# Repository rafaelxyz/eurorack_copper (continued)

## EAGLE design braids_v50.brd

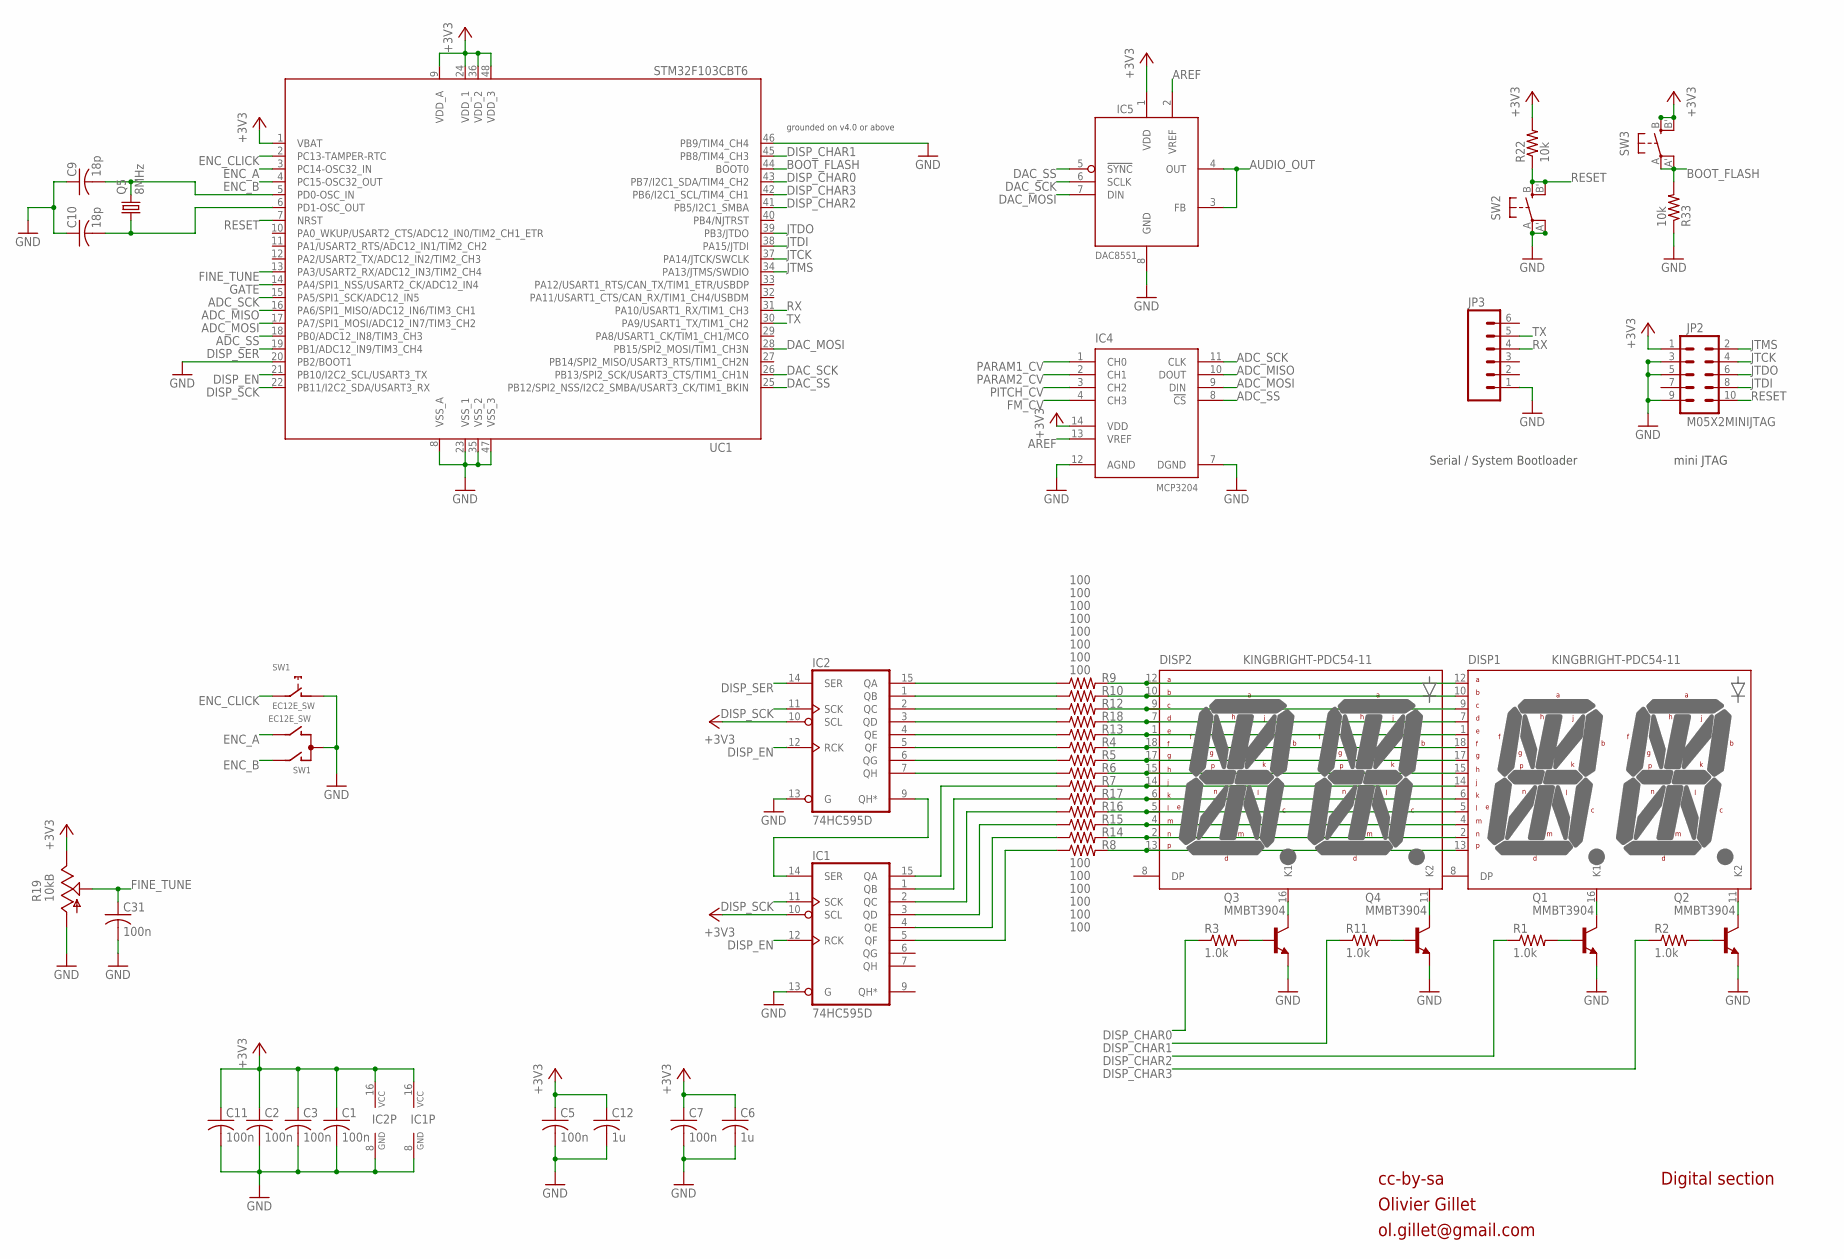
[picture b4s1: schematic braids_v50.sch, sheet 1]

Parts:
C1, C2, C3, C5, C7, C11, C31: 100n; C0603
C6, C12: 1u; C0603
C9, C10: 18p; C0603
DISP1, DISP2: KINGBRIGHT-PDC54-11; PDC54
IC1, IC2: 74HC595D; SO16
IC4: MCP3204; SO14
IC5: DAC8551; MSOP-8
JP2: M05X2MINIJTAG; 2X5-1.27
JP3: M06SIP; 1X06
Q1, Q2, Q3, Q4: MMBT3904; SOT23-BEC
Q5: 8MHz; HC49UP
R1, R2, R3, R11: 1.0k; R0603
R4, R5, R6, R7, R8, R9, R10, R12, R13, R14, R15, R16, R17, R18: 100; R0603
R19: 10kB; ALPS_POT_VERTICAL_PS
R22, R33: 10k; R0603
SW1: EC12E_SW; ALPS_EC12E_SW
SW2, SW3: EVQQ2; EVQ-Q2
UC1: STM32F103CBT6; LQFP48

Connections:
+3V3: C1.1, C2.1, C3.1, C5.1, C6.1, C7.1, C11.1, C12.1, IC1.10 (SCL), IC1.16 (VCC), IC2.10 (SCL), IC2.16 (VCC), IC4.14 (VDD), IC5.1 (VDD), JP2.1, R19.P$1 (E), R22.2, SW3.B (S), SW3.B' (S1), UC1.1 (VBAT), UC1.9 (VDD_A), UC1.24 (VDD_1), UC1.36 (VDD_2), UC1.48 (VDD_3); also elsewhere on the board
ADC_MISO: IC4.10 (DOUT), UC1.16 (PA6/SPI1_MISO/ADC12_IN6/TIM3_CH1)
ADC_MOSI: IC4.9 (DIN), UC1.17 (PA7/SPI1_MOSI/ADC12_IN7/TIM3_CH2)
ADC_SCK: IC4.11 (CLK), UC1.15 (PA5/SPI1_SCK/ADC12_IN5)
ADC_SS: IC4.8 (!CS), UC1.18 (PB0/ADC12_IN8/TIM3_CH3)
AREF: IC4.13 (VREF), IC5.2 (VREF); also elsewhere on the board
AUDIO_OUT: IC5.3 (FB), IC5.4 (OUT); also elsewhere on the board
BOOT_FLASH: R33.2, SW3.A, SW3.A' (P1), UC1.44 (BOOT0)
DAC_MOSI: IC5.7 (DIN), UC1.28 (PB15/SPI2_MOSI/TIM1_CH3N)
DAC_SCK: IC5.6 (SCLK), UC1.26 (PB13/SPI2_SCK/USART3_CTS/TIM1_CH1N)
DAC_SS: IC5.5 (!SYNC), UC1.25 (PB12/SPI2_NSS/I2C2_SMBA/USART3_CK/TIM1_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)
DISP_CHAR0: R3.1, UC1.43 (PB7/I2C1_SDA/TIM4_CH2)
DISP_CHAR1: R11.1, UC1.45 (PB8/TIM4_CH3)
DISP_CHAR2: R1.1, UC1.41 (PB5/I2C1_SMBA)
DISP_CHAR3: R2.1, UC1.42 (PB6/I2C1_SCL/TIM4_CH1)
DISP_EN: IC1.12 (RCK), IC2.12 (RCK), UC1.21 (PB10/I2C2_SCL/USART3_TX)
DISP_SCK: IC1.11 (SCK), IC2.11 (SCK), UC1.22 (PB11/I2C2_SDA/USART3_RX)
DISP_SER: IC2.14 (SER), UC1.19 (PB1/ADC12_IN9/TIM3_CH4)
ENC_A: SW1.B, UC1.3 (PC14-OSC32_IN)
ENC_B: SW1.A, UC1.4 (PC15-OSC32_OUT)
ENC_CLICK: SW1.E (2), UC1.2 (PC13-TAMPER-RTC)
FINE_TUNE: C31.1, R19.P$2 (S), UC1.13 (PA3/USART2_RX/ADC12_IN3/TIM2_CH4)
FM_CV: IC4.4 (CH3); also elsewhere on the board
GATE: UC1.14 (PA4/SPI1_NSS/USART2_CK/ADC12_IN4); also elsewhere on the board
GND: C1.2, C2.2, C3.2, C5.2, C6.2, C7.2, C9.1, C10.1, C11.2, C12.2, C31.2, IC1.8 (GND), IC1.13 (G), IC2.8 (GND), IC2.13 (G), IC4.7 (DGND), IC4.12 (AGND), IC5.8 (GND), JP2.3, JP2.5, JP2.9, JP3.1, Q1.E, Q2.E, Q3.E, Q4.E, R19.P$3 (A), R33.1, SW1.C, SW1.D (1), SW2.A, SW2.A' (P1), UC1.8 (VSS_A), UC1.20 (PB2/BOOT1), UC1.23 (VSS_1), UC1.35 (VSS_2), UC1.46 (PB9/TIM4_CH4), UC1.47 (VSS_3); also elsewhere on the board
JTCK: JP2.4, UC1.37 (PA14/JTCK/SWCLK)
JTDI: JP2.8, UC1.38 (PA15/JTDI)
JTDO: JP2.6, UC1.39 (PB3/JTDO)
JTMS: JP2.2, UC1.34 (PA13/JTMS/SWDIO)
unnamed: DISP2.16 (K1), Q3.C
unnamed: DISP2.11 (K2), Q4.C
unnamed: DISP1.16 (K1), Q1.C
unnamed: DISP1.11 (K2), Q2.C
unnamed: Q3.B, R3.2
unnamed: Q4.B, R11.2
unnamed: C9.2, Q5.2, UC1.5 (PD0-OSC_IN)
unnamed: C10.2, Q5.1, UC1.6 (PD1-OSC_OUT)
unnamed: Q1.B, R1.2
unnamed: Q2.B, R2.2
unnamed: DISP1.12 (A), DISP2.12 (A), R9.2
unnamed: DISP1.10 (B), DISP2.10 (B), R10.2
unnamed: DISP1.9 (C), DISP2.9 (C), R12.2
unnamed: DISP1.7 (D), DISP2.7 (D), R18.2
unnamed: DISP1.1 (E), DISP2.1 (E), R13.2
unnamed: DISP1.18 (F), DISP2.18 (F), R4.2
unnamed: DISP1.17 (G), DISP2.17 (G), R5.2
unnamed: DISP1.15 (H), DISP2.15 (H), R6.2
unnamed: DISP1.14 (J), DISP2.14 (J), R7.2
unnamed: DISP1.6 (K), DISP2.6 (K), R17.2
unnamed: DISP1.5 (L), DISP2.5 (L), R16.2
unnamed: DISP1.4 (M), DISP2.4 (M), R15.2
unnamed: DISP1.2 (N), DISP2.2 (N), R14.2
unnamed: DISP1.13, DISP2.13, R8.2
unnamed: IC2.7 (QH), R6.1
unnamed: IC1.14 (SER), IC2.9 (QH*)
unnamed: IC2.15 (QA), R9.1
unnamed: IC2.1 (QB), R10.1
unnamed: IC2.2 (QC), R12.1
unnamed: IC2.3 (QD), R18.1
unnamed: IC2.4 (QE), R13.1
unnamed: IC2.5 (QF), R4.1
unnamed: IC2.6 (QG), R5.1
unnamed: IC1.15 (QA), R7.1
unnamed: IC1.1 (QB), R17.1
unnamed: IC1.2 (QC), R16.1
unnamed: IC1.3 (QD), R15.1
unnamed: IC1.4 (QE), R14.1
unnamed: IC1.5 (QF), R8.1
PARAM1_CV: IC4.1 (CH0); also elsewhere on the board
PARAM2_CV: IC4.2 (CH1); also elsewhere on the board
PITCH_CV: IC4.3 (CH2); also elsewhere on the board
RESET: JP2.10, R22.1, SW2.B (S), SW2.B' (S1), UC1.7 (NRST)
RX: JP3.4, UC1.31 (PA10/USART1_RX/TIM1_CH3)
TX: JP3.5, UC1.30 (PA9/USART1_TX/TIM1_CH2)

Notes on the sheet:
cc-by-sa
Olivier Gillet
ol.gillet@gmail.com
Serial / System Bootloader
mini JTAG
Digital section
grounded on v4.0 or above

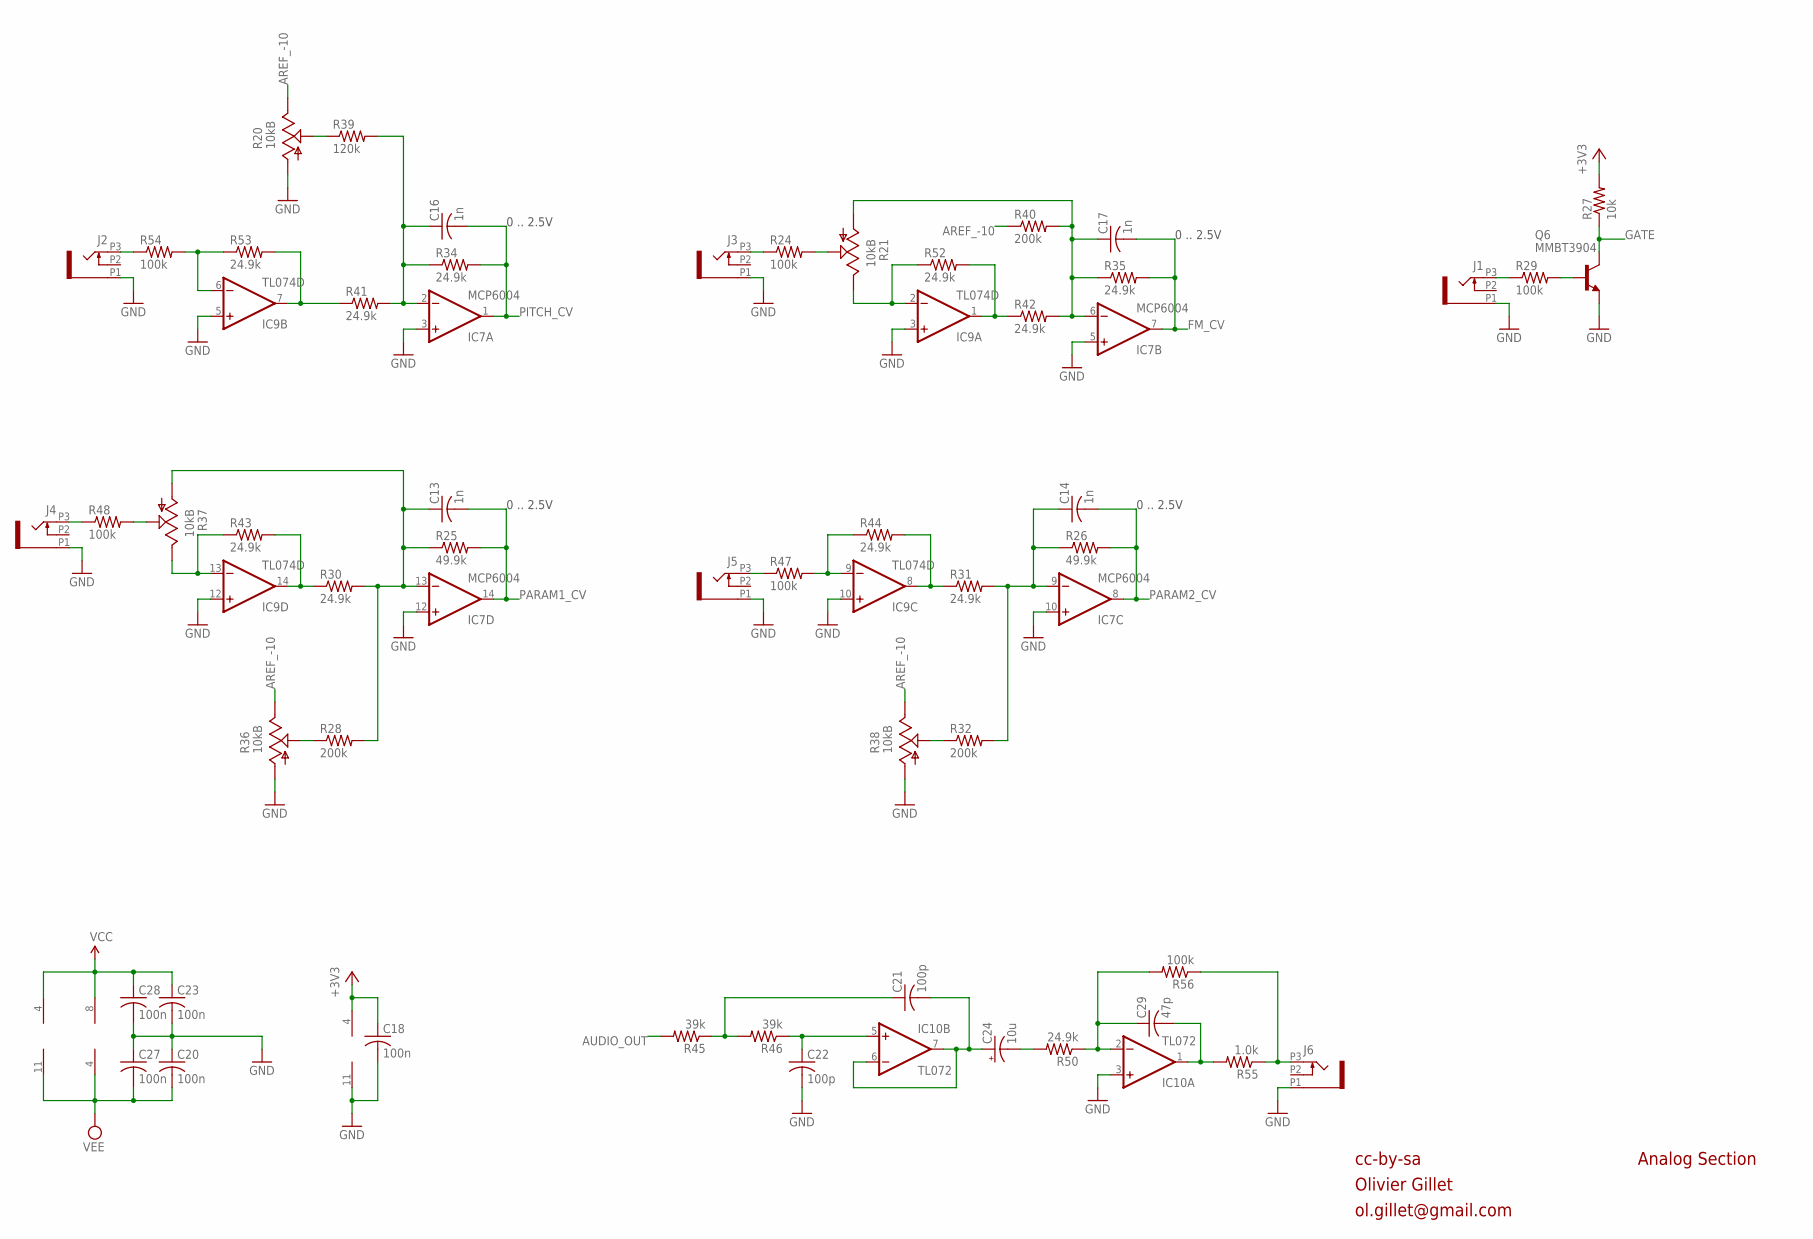
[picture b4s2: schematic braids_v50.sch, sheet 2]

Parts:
C13, C14, C16, C17: 1n; C0603
C18, C20, C23, C27, C28: 100n; C0603
C21, C22: 100p; C0603
C24: 10u; PANASONIC_B
C29: 47p; C0603
IC7: MCP6004; SO14
IC9: TL074D; SO14
IC10: TL072; SO08
J1, J2, J3, J4, J5, J6: PJ301_THONKICONN6; WQP_PJ_301M6
Q6: MMBT3904; SOT23-BEC
R20, R21, R36, R37, R38: 10kB; ALPS_POT_VERTICAL_PS
R24, R29, R47, R48, R54, R56: 100k; R0603
R25, R26: 49.9k; R0603
R27: 10k; R0603
R28, R32, R40: 200k; R0603
R30, R31, R34, R35, R41, R42, R43, R44, R50, R52, R53: 24.9k; R0603
R39: 120k; R0603
R45, R46: 39k; R0603
R55: 1.0k; R0603

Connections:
+3V3: C18.1, IC7.4 (V+), R27.2; also elsewhere on the board
AREF_-10: R20.P$1 (E), R36.P$1 (E), R38.P$1 (E), R40.1; also elsewhere on the board
AUDIO_OUT: R45.2; also elsewhere on the board
FM_CV: C17.2, IC7.7 (OUT), R35.2; also elsewhere on the board
GATE: Q6.C, R27.1; also elsewhere on the board
GND: C18.2, C20.1, C22.2, C23.2, C27.1, C28.2, IC7.3 (+IN), IC7.5 (+IN), IC7.10 (+IN), IC7.11 (V-), IC7.12 (+IN), IC9.3 (+IN), IC9.5 (+IN), IC9.10 (+IN), IC9.12 (+IN), IC10.3 (+IN), J1.P1 (1), J2.P1 (1), J3.P1 (1), J4.P1 (1), J5.P1 (1), J6.P1 (1), Q6.E, R20.P$3 (A), R36.P$3 (A), R38.P$3 (A); also elsewhere on the board
unnamed: IC9.7 (OUT), R41.1, R53.2
unnamed: R20.P$2 (S), R39.1
unnamed: J2.P3 (3), R54.1
unnamed: C16.1, IC7.2 (-IN), R34.1, R39.2, R41.2
unnamed: IC9.6 (-IN), R53.1, R54.2
unnamed: J3.P3 (3), R24.1
unnamed: J4.P3 (3), R48.1
unnamed: R21.P$2 (S), R24.2
unnamed: IC9.13 (-IN), R37.P$1 (E), R43.1
unnamed: IC9.14 (OUT), R30.1, R43.2
unnamed: IC9.2 (-IN), R21.P$1 (E), R52.1
unnamed: IC9.1 (OUT), R42.1, R52.2
unnamed: C17.1, IC7.6 (-IN), R21.P$3 (A), R35.1, R40.2, R42.2
unnamed: J1.P3 (3), R29.1
unnamed: IC9.8 (OUT), R31.1, R44.2
unnamed: C13.1, IC7.13 (-IN), R25.1, R28.2, R30.2, R37.P$3 (A)
unnamed: J5.P3 (3), R47.1
unnamed: R28.1, R36.P$2 (S)
unnamed: R37.P$2 (S), R48.2
unnamed: IC9.9 (-IN), R44.1, R47.2
unnamed: R32.1, R38.P$2 (S)
unnamed: Q6.B, R29.2
unnamed: C21.2, C24.+, IC10.6 (-IN), IC10.7 (OUT)
unnamed: C24.-, R50.2
unnamed: C22.1, IC10.5 (+IN), R46.1
unnamed: C14.1, IC7.9 (-IN), R26.1, R31.2, R32.2
unnamed: C21.1, R45.1, R46.2
unnamed: J6.P3 (3), R55.1, R56.1
unnamed: C29.2, IC10.1 (OUT), R55.2
unnamed: C29.1, IC10.2 (-IN), R50.1, R56.2
PARAM1_CV: C13.2, IC7.14 (OUT), R25.2; also elsewhere on the board
PARAM2_CV: C14.2, IC7.8 (OUT), R26.2; also elsewhere on the board
PITCH_CV: C16.2, IC7.1 (OUT), R34.2; also elsewhere on the board
VCC: C23.1, C28.1, IC9.4 (V+), IC10.8 (V+); also elsewhere on the board
VEE: C20.2, C27.2, IC9.11 (V-), IC10.4 (V-); also elsewhere on the board

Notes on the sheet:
cc-by-sa
Olivier Gillet
ol.gillet@gmail.com
Analog Section
0 .. 2.5V

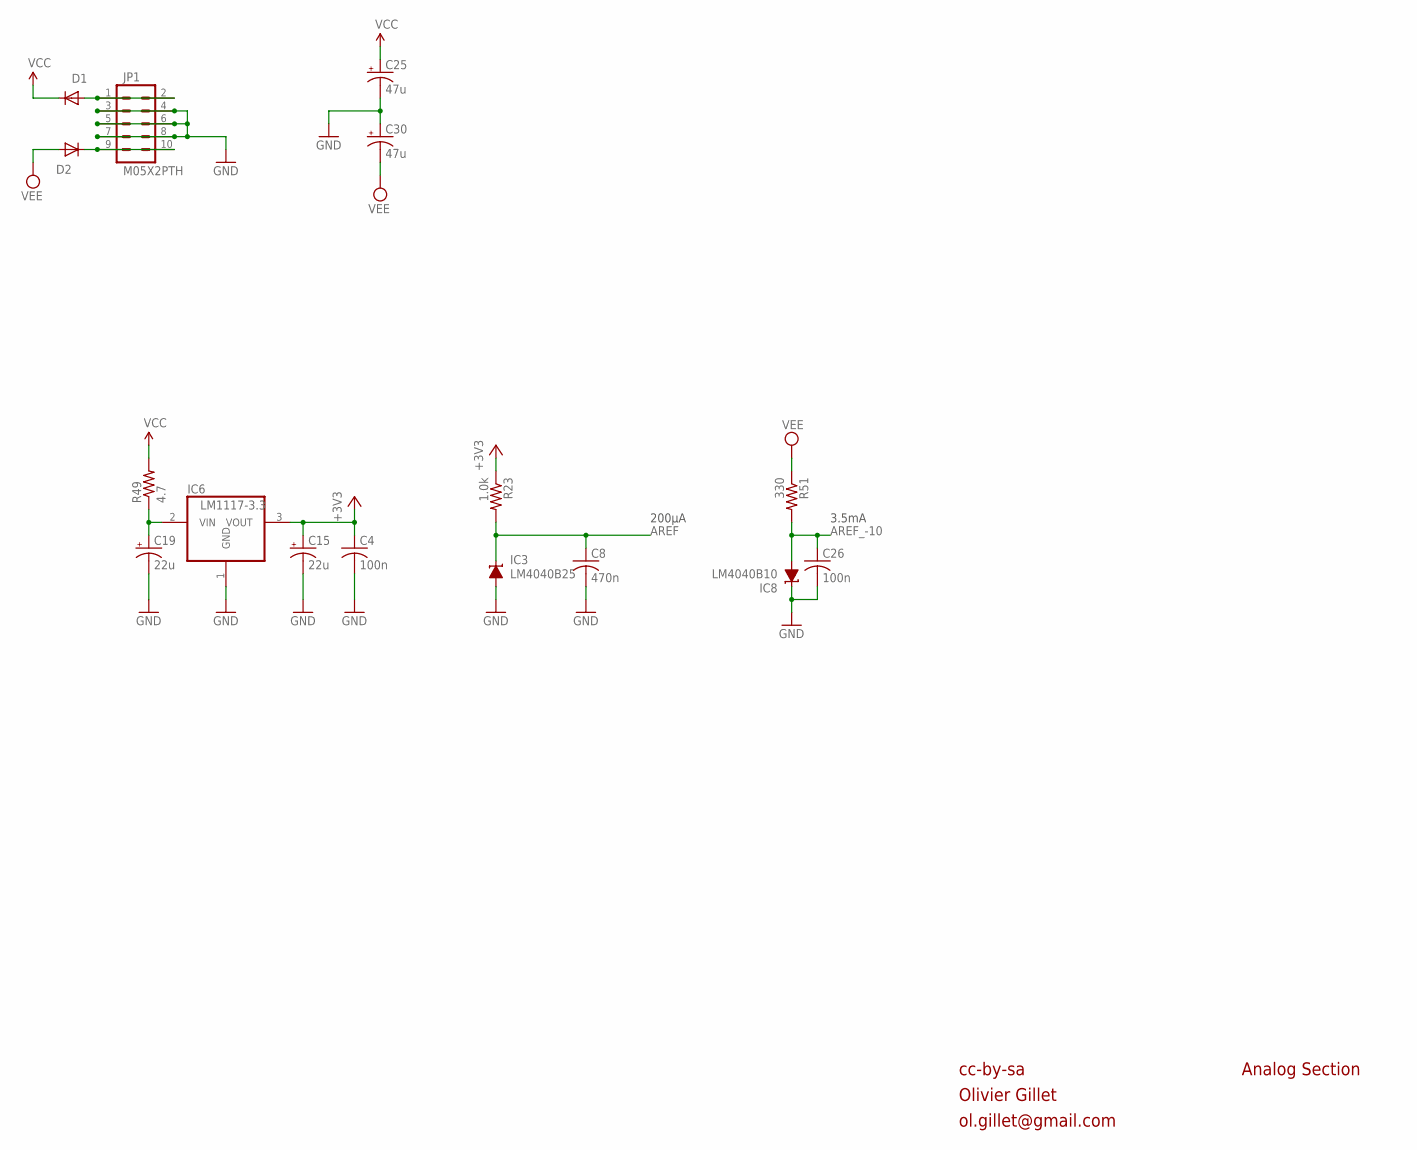
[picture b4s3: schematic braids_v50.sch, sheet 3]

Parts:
C4, C26: 100n; C0603
C8: 470n; C0603
C15, C19: 22u; PANASONIC_C
C25, C30: 47u; PANASONIC_D
D1, D2: 1N5819HW; SOD123
IC3: LM4040B25; DBZ_R-PDSO-G3
IC6: LM1117-3.3; TO252
IC8: LM4040B10; DBZ_R-PDSO-G3
JP1: M05X2PTH; AVR_ICSP
R23: 1.0k; R0603
R49: 4.7; R1206
R51: 330; R0603

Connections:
+3V3: C4.1, C15.+, IC6.3 (VOUT), R23.1; also elsewhere on the board
AREF: C8.1, IC3.1 (C), R23.2; also elsewhere on the board
AREF_-10: C26.1, IC8.2 (A), R51.2; also elsewhere on the board
GND: C4.2, C8.2, C15.-, C19.-, C25.-, C26.2, C30.+, IC3.2 (A), IC6.1 (GND), IC8.1 (C), JP1.3, JP1.4, JP1.5, JP1.6, JP1.7, JP1.8; also elsewhere on the board
unnamed: C19.+, IC6.2 (VIN), R49.1
unnamed: D1.A, JP1.1, JP1.2
unnamed: D2.C, JP1.9, JP1.10
VCC: C25.+, D1.C, R49.2; also elsewhere on the board
VEE: C30.-, D2.A, R51.1; also elsewhere on the board

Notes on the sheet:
3.5mA
200µA
cc-by-sa
Olivier Gillet
ol.gillet@gmail.com
Analog Section

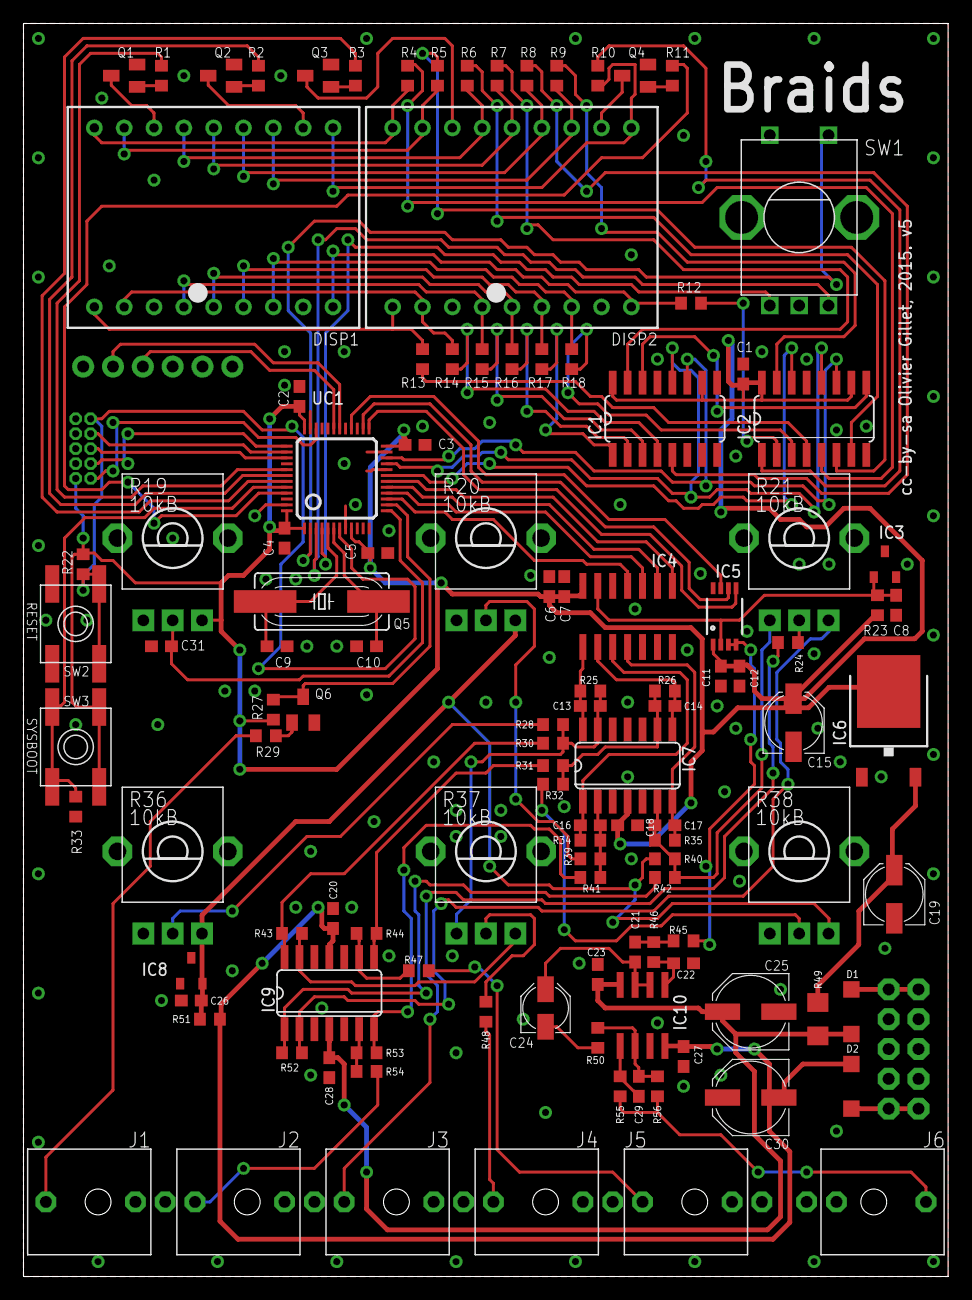
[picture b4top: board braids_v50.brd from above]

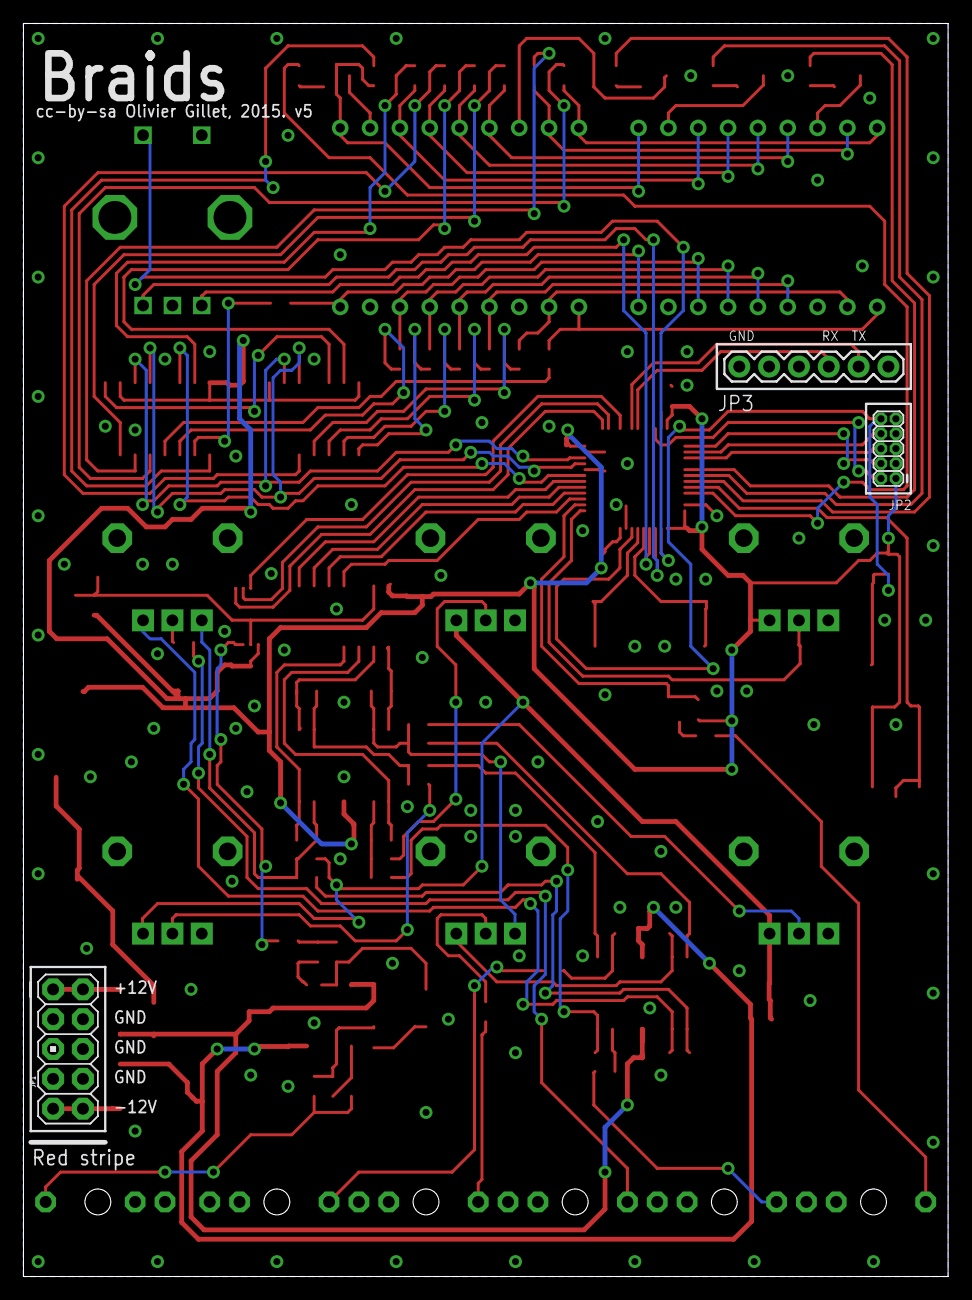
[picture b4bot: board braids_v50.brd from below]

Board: 2 copper layers, 78.7 x 106.7 mm, 120 parts (3 on the bottom side), 110 nets.

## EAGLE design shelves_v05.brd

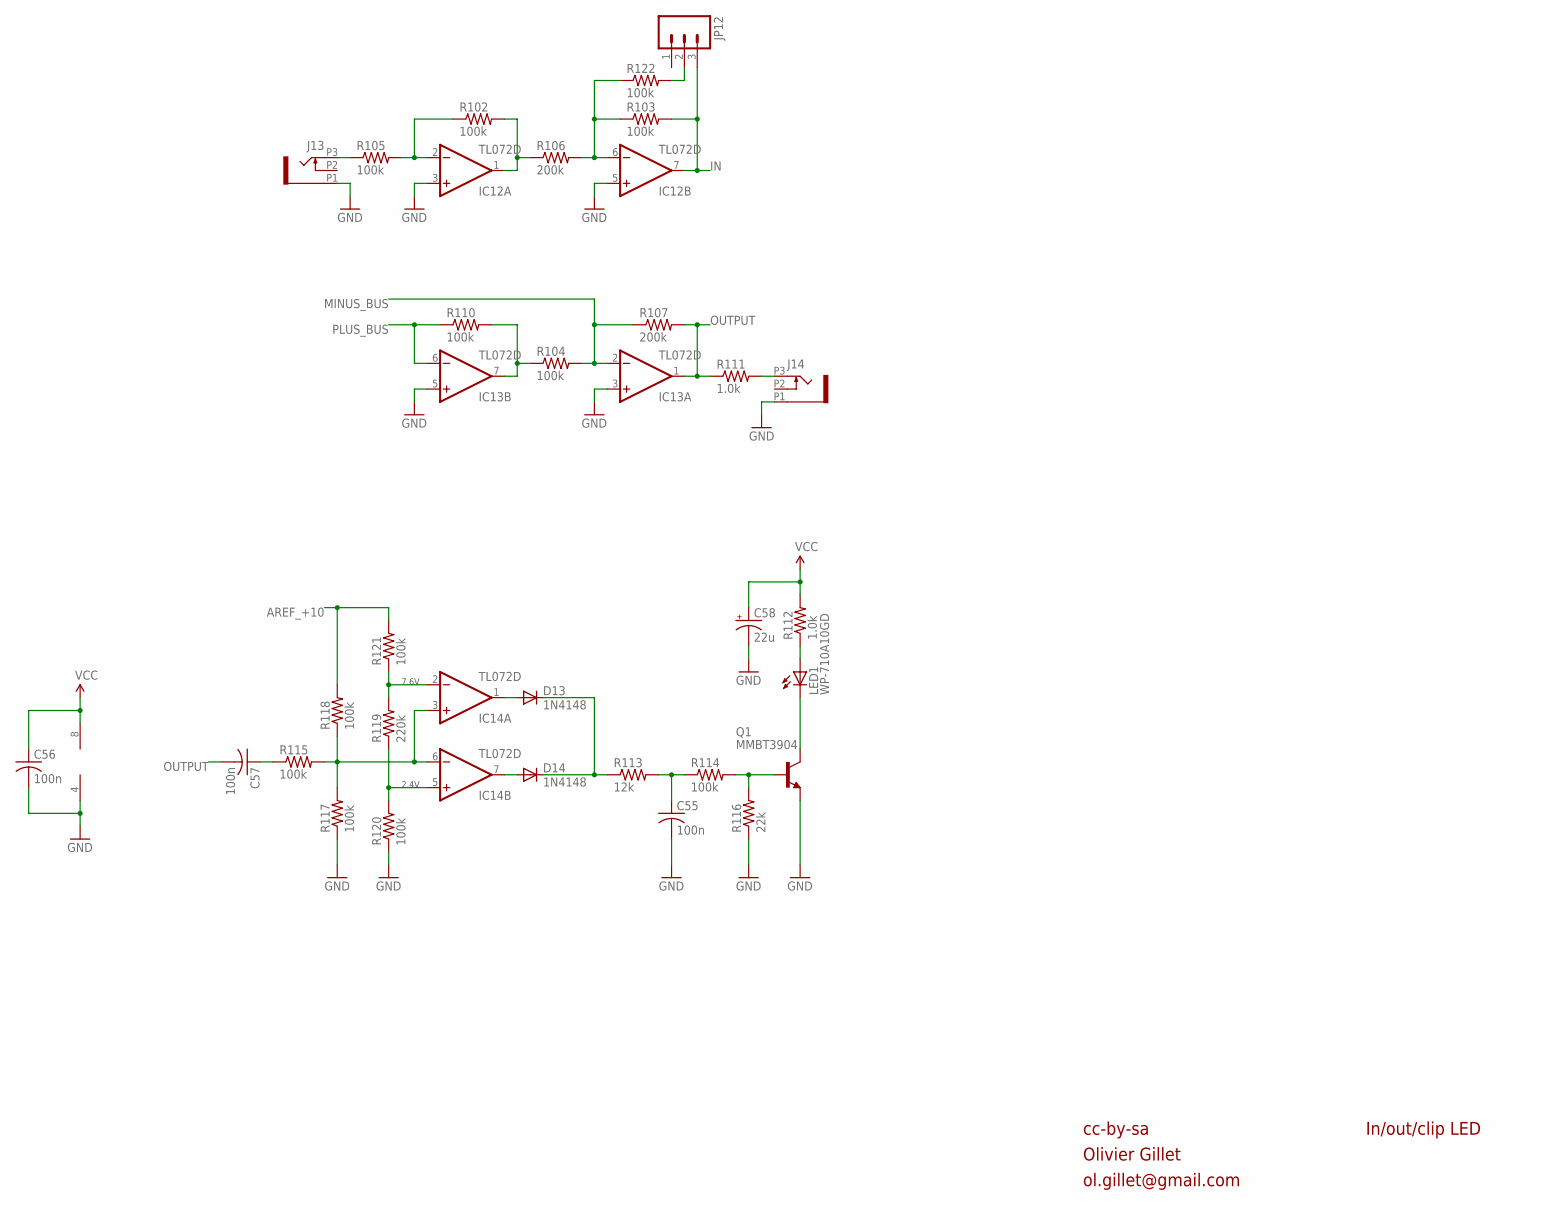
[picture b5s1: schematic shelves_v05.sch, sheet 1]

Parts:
C55, C56, C57: 100n; C0603
C58: 22u; PANASONIC_C
D13, D14: 1N4148; SOD323-W
IC12, IC13, IC14: TL072D; SO08
J13, J14: PJ301_THONKICONN6; WQP_PJ_301M6
JP12: M03PTH; 1X03
LED1: WP-710A10GD; LED3MM
Q1: MMBT3904; SOT23-BEC
R102, R103, R104, R105, R110, R114, R115, R117, R118, R120, R121, R122: 100k; R0603
R106, R107: 200k; R0603
R111, R112: 1.0k; R0603
R113: 12k; R0603
R116: 22k; R0603
R119: 220k; R0603

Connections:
AREF_+10: R118.2, R121.2; also elsewhere on the board
GND: C55.2, C56.2, C58.-, IC12.3 (+IN), IC12.5 (+IN), IC13.3 (+IN), IC13.5 (+IN), IC14.4 (V-), J13.P1 (1), J14.P1 (1), Q1.E, R116.1, R117.1, R120.1; also elsewhere on the board
IN: IC12.7 (OUT), JP12.3, R103.2; also elsewhere on the board
IN_INV: IC12.1 (OUT), R102.2, R106.1
IN_INV1: IC13.7 (OUT), R104.1, R110.2
J_IN: J13.P3 (3), R105.1
MINUS_BUS: IC13.2 (-IN), R104.2, R107.1; also elsewhere on the board
unnamed: JP12.2, R122.2
unnamed: IC12.2 (-IN), R102.1, R105.2
unnamed: IC12.6 (-IN), R103.1, R106.2, R122.1
unnamed: LED1.K (C), Q1.C
unnamed: J14.P3 (3), R111.2
unnamed: C57.1, R115.1
unnamed: IC14.3 (+IN), IC14.6 (-IN), R115.2, R117.2, R118.1
unnamed: IC14.2 (-IN), R119.2, R121.1
unnamed: C55.1, R113.2, R114.1
unnamed: IC14.5 (+IN), R119.1, R120.2
unnamed: D13.A, IC14.1 (OUT)
unnamed: D14.A, IC14.7 (OUT)
unnamed: D13.C, D14.C, R113.1
unnamed: LED1.A, R112.1
unnamed: Q1.B, R114.2, R116.2
OUTPUT: C57.2, IC13.1 (OUT), R107.2, R111.1
PLUS_BUS: IC13.6 (-IN), R110.1; also elsewhere on the board
VCC: C56.1, C58.+, IC14.8 (V+), R112.2; also elsewhere on the board

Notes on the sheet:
cc-by-sa
Olivier Gillet
ol.gillet@gmail.com
In/out/clip LED
2.4V
7.6V

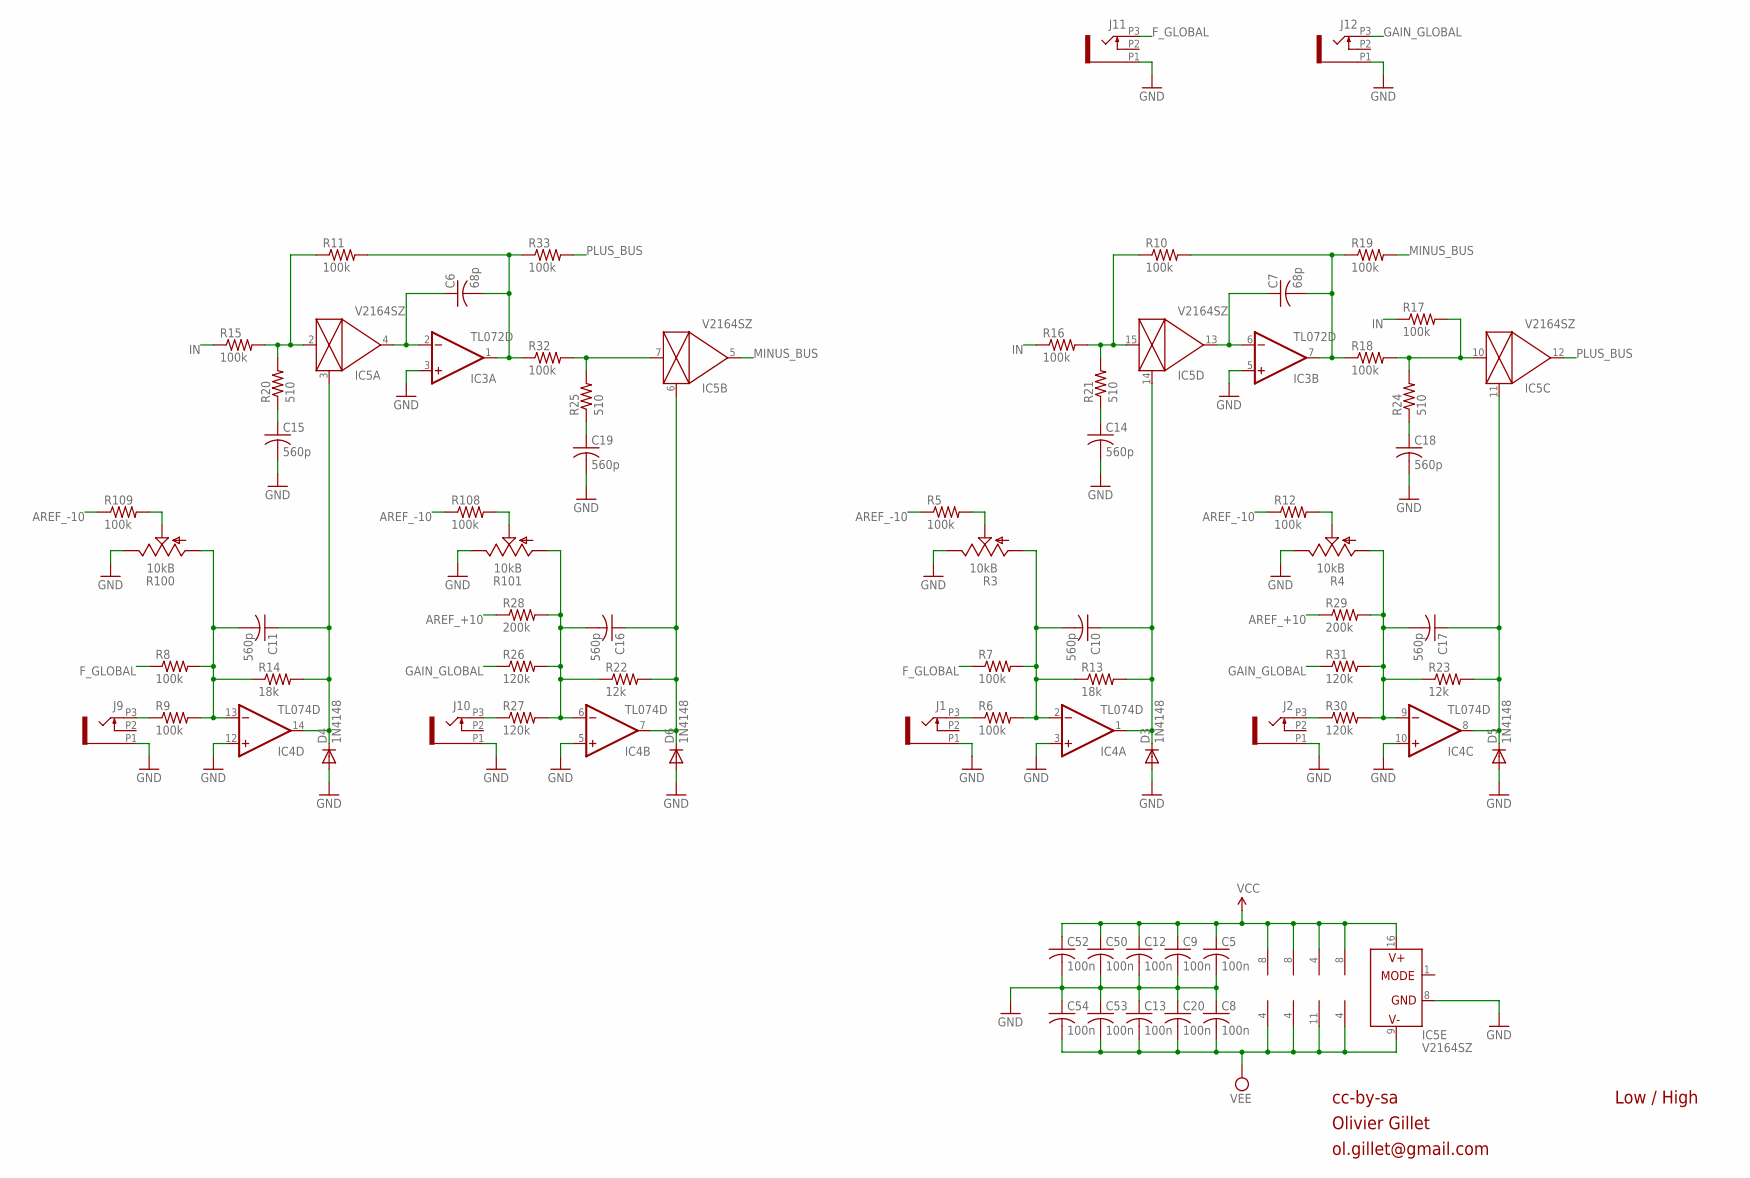
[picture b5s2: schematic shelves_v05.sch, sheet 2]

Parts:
C5, C8, C9, C12, C13, C20, C50, C52, C53, C54: 100n; C0603
C6, C7: 68p; C0603
C10, C11, C14, C15, C16, C17, C18, C19: 560p; C0603
D3, D4, D5, D6: 1N4148; SOD323-W
IC3, IC12, IC13: TL072D; SO08
IC4: TL074D; SO14
IC5: V2164SZ; SOIC16N
J1, J2, J9, J10, J11, J12: PJ301_THONKICONN6; WQP_PJ_301M6
R3, R4, R100, R101: 10kB; ALPS_POT_VERTICAL_PS
R5, R6, R7, R8, R9, R10, R11, R12, R15, R16, R17, R18, R19, R32, R33, R108, R109: 100k; R0603
R13, R14: 18k; R0603
R20, R21, R24, R25: 510; R0603
R22, R23: 12k; R0603
R26, R27, R30, R31: 120k; R0603
R28, R29: 200k; R0603

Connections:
AREF_+10: R28.1, R29.1; also elsewhere on the board
AREF_-10: R5.1, R12.1, R108.1, R109.1; also elsewhere on the board
F_GLOBAL: J11.P3 (3), R7.1, R8.1; also elsewhere on the board
GAIN_GLOBAL: J12.P3 (3), R26.1, R31.1; also elsewhere on the board
GND: C5.2, C8.1, C9.2, C12.2, C13.1, C14.2, C15.2, C18.2, C19.2, C20.1, C50.2, C52.2, C53.1, C54.1, D3.A, D4.A, D5.A, D6.A, IC3.3 (+IN), IC3.5 (+IN), IC4.3 (+IN), IC4.5 (+IN), IC4.10 (+IN), IC4.12 (+IN), IC5.8 (GND), J1.P1 (1), J2.P1 (1), J9.P1 (1), J10.P1 (1), J11.P1 (1), J12.P1 (1), R3.P$1 (E), R4.P$1 (E), R100.P$1 (E), R101.P$1 (E); also elsewhere on the board
IN: R15.1, R16.1, R17.1; also elsewhere on the board
J_HF_CV: J2.P3 (3), R30.1
J_HF_F: J1.P3 (3), R6.1
J_LF_CV: J10.P3 (3), R27.1
J_LF_F: J9.P3 (3), R9.1
LP: C6.2, IC3.1 (OUT), R11.2, R32.1, R33.1
LP1: C7.2, IC3.7 (OUT), R10.2, R18.1, R19.1
MINUS_BUS: IC5.5 (OUT), R19.2; also elsewhere on the board
unnamed: IC5.2 (IN), R11.1, R15.2, R20.2
unnamed: C19.1, R25.1
unnamed: C11.1, D4.C, IC4.14 (OUT), IC5.3 (CTRL), R14.2
unnamed: C6.1, IC3.2 (-IN), IC5.4 (OUT)
unnamed: C14.1, R21.1
unnamed: C16.1, D6.C, IC4.7 (OUT), IC5.6 (CTRL), R22.2
unnamed: C15.1, R20.1
unnamed: R100.P$2 (S), R109.2
unnamed: C16.2, IC4.6 (-IN), R22.1, R26.2, R27.2, R28.2, R101.P$3 (A)
unnamed: R101.P$2 (S), R108.2
unnamed: IC5.15 (IN), R10.1, R16.2, R21.2
unnamed: IC5.7 (IN), R25.2, R32.2
unnamed: C11.2, IC4.13 (-IN), R8.2, R9.2, R14.1, R100.P$3 (A)
unnamed: C7.1, IC3.6 (-IN), IC5.13 (OUT)
unnamed: R3.P$2 (S), R5.2
unnamed: C17.1, D5.C, IC4.8 (OUT), IC5.11 (CTRL), R23.2
unnamed: C17.2, IC4.9 (-IN), R4.P$3 (A), R23.1, R29.2, R30.2, R31.2
unnamed: R4.P$2 (S), R12.2
unnamed: C10.2, IC4.2 (-IN), R3.P$3 (A), R6.2, R7.2, R13.1
unnamed: C18.1, R24.1
unnamed: IC5.10 (IN), R17.2, R18.2, R24.2
unnamed: C10.1, D3.C, IC4.1 (OUT), IC5.14 (CTRL), R13.2
PLUS_BUS: IC5.12 (OUT), R33.2; also elsewhere on the board
VCC: C5.1, C9.1, C12.1, C50.1, C52.1, IC3.8 (V+), IC4.4 (V+), IC5.16 (V+), IC12.8 (V+), IC13.8 (V+); also elsewhere on the board
VEE: C8.2, C13.2, C20.2, C53.2, C54.2, IC3.4 (V-), IC4.11 (V-), IC5.9 (V-), IC12.4 (V-), IC13.4 (V-); also elsewhere on the board

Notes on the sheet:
cc-by-sa
Olivier Gillet
ol.gillet@gmail.com
Low / High
